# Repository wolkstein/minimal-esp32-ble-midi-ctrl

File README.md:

# Minimal ESP32 BLE Midi Control Interface

This project is a minimal ESP32 BLE MIDI controller. It allows you to control MIDI devices wirelessly using Bluetooth Low Energy (BLE) technology. The controller is designed to be compact and easy to use, making it ideal for musicians and performers.

## Features

- BLE MIDI connectivity
- Compact and portable design
- Easy-to-use interface
- Easy-to-use Web UI to make settings
- Online Firmware Update
- With Ardour and Harrison Mixbus compatible midi_map file
- as Platformio Project (esp32 arduino framework)

## Parts
- ESP32-S3-Mini
- 5 momentary button switches
- 5 10k resistors
- breadboard
- optional rgb led ws28xx

## PCB Version with Lipo and Battery Charger

PCB:

Housing:

## Getting Started

To get started with the project, follow these steps:

1. Clone the repository: `$ git clone https://github.com/wolkstein/minimal-esp32-ble-midi-ctrl`
2. Open as Platformio Project for example with VSC Pio Extension
3. Connect your ESP32 device to your computer via USB.
4. Change the platformio.ini as you need
5. Press PIO upload button
6. Your ESP32 BLE MIDI controller is now ready to use!

## Contributing

Contributions are welcome! If you have any ideas, suggestions, or bug reports, please open an issue or submit a pull request.

## License

This project is licensed under the GNU General Public License v3.0. See the [LICENSE](LICENSE) file for more information.

## Linux howto BlueZ with MIDI over BLE Support

Nice Howto from Peter P:

https://tttapa.github.io/Pages/Ubuntu/Software-Installation/BlueZ.html

After compiling BlueZ, Little Helper shown in Catja App

## Ardour / Mixbus Midi Setup

- For example copy the Midi Map file from this Repo like this:
```bash
cp DAW_MIDI_MAPS/ArdourAndHarrisonMixbus/midi_mapsLittle_Helper.map ~/.config/ardour6/midi_maps
```
- Now you can open the Edit-Preferences Window in Ardour, and under Control Surfaces, select Generic Midi
- Press Show Protocol Settings
- Now you can select "Little_Helper" in Midi Bindings dropdown
- if Little Helper is already connected via bluetooth you can make connection in Incoming Midi Dropdown like in the Image below
- Done  

---
## Some more pictures of how it is used

### All parts

### Guitar attachment

### Web interface

---
## Simple Manual

### First Wi-Fi Connection and Settings

#### To connect to the built-in access point, follow these steps:

1. Power on your ESP32 BLE MIDI controller while pressing Btn 4 and 5
2. Wait til LED becomes Blue
3. Once initialized, the controller will start broadcasting its own access point (AP) named "LittleHelperAP-xxx"
4. On your computer or mobile device, go to the Wi-Fi settings and connect to the "LittleHelperAP-xxx" network.
5. Open a web browser and enter the following URL: `http://192.168.8.1`.
6. You will be redirected to the controller's web interface.
7. In the web interface, navigate to the "Settings" Tab.

After completing the initial steps, the device is now capable of connecting to a local network. If the user desires, they can hold down buttons 4 and 5 while powering down the device. This will allow the device to connect to a local Wi-Fi network and start the web UI for making MIDI settings, if necessary.

## Firmware Update over WiFi Connection

To update the firmware of your ESP32 BLE MIDI controller over a WiFi connection, follow these steps:

1. Ensure that your ESP32 BLE MIDI controller is connected to your local WiFi network. You can do this by navigating to the "Settings" tab in the controller's web interface and entering your WiFi credentials.

2. Once connected, go to the Settings Tab and check the label that displays the current firmware version (e.g., s3miniVx).

3. Visit the GitHub project page for Little Helper and go to the "Binary" folder (https://github.com/wolkstein/minimal-esp32-ble-midi-ctrl/tree/main/bin) to check if there is a newer firmware available. Look for a firmware version number that is higher than the one displayed in the firmware label.

4. If a newer firmware is available, you can proceed with the update.

5. In the Settings Tab, click the "Try Update" button to request the firmware update.

6. After clicking the button, you will see a message saying "Update Requested, need Reboot".

7. Turn off the power to your ESP32 BLE MIDI controller by switching the power switch to the "off" position and removing the USB cable.

8. Power on the device again either by switching the power switch back on or by connecting the USB cable.

9. Wait for the LED on the device to turn yellow. This indicates that the device is in update mode and is connected to your local network.

10. If the LED starts blinking purple, it means that the update process is running. Wait until the LED switches back to its normal red or green light. If the LED does not blink purple, it means that the device has rebooted without performing the update.

11. If the update fails, you can simply try again. If something goes wrong during the update, the previous firmware will be automatically recovered.

12. If the update is successful, you can reconnect to the web interface and check the firmware version label to confirm the update.

---
# Button Combinations at Power up

This section describes the button combinations and their corresponding functions that can be used during power up.
Btn 1 to btn 5 from left to right.

| Button Combination | Function                                                  |
| ----------------- | --------------------------------------------------------- |
| o o o x x         | Connect To Local Wifi Network and enable Web UI            |
| o o x x x         | Start AP Mode and enable Web UI                            |
| x x o o o         | Reset Midi Settings to Default                            |
| x o x o o         | Reset Midi Settings and Wifi Settings to Default          |

x = pressed,
o = released

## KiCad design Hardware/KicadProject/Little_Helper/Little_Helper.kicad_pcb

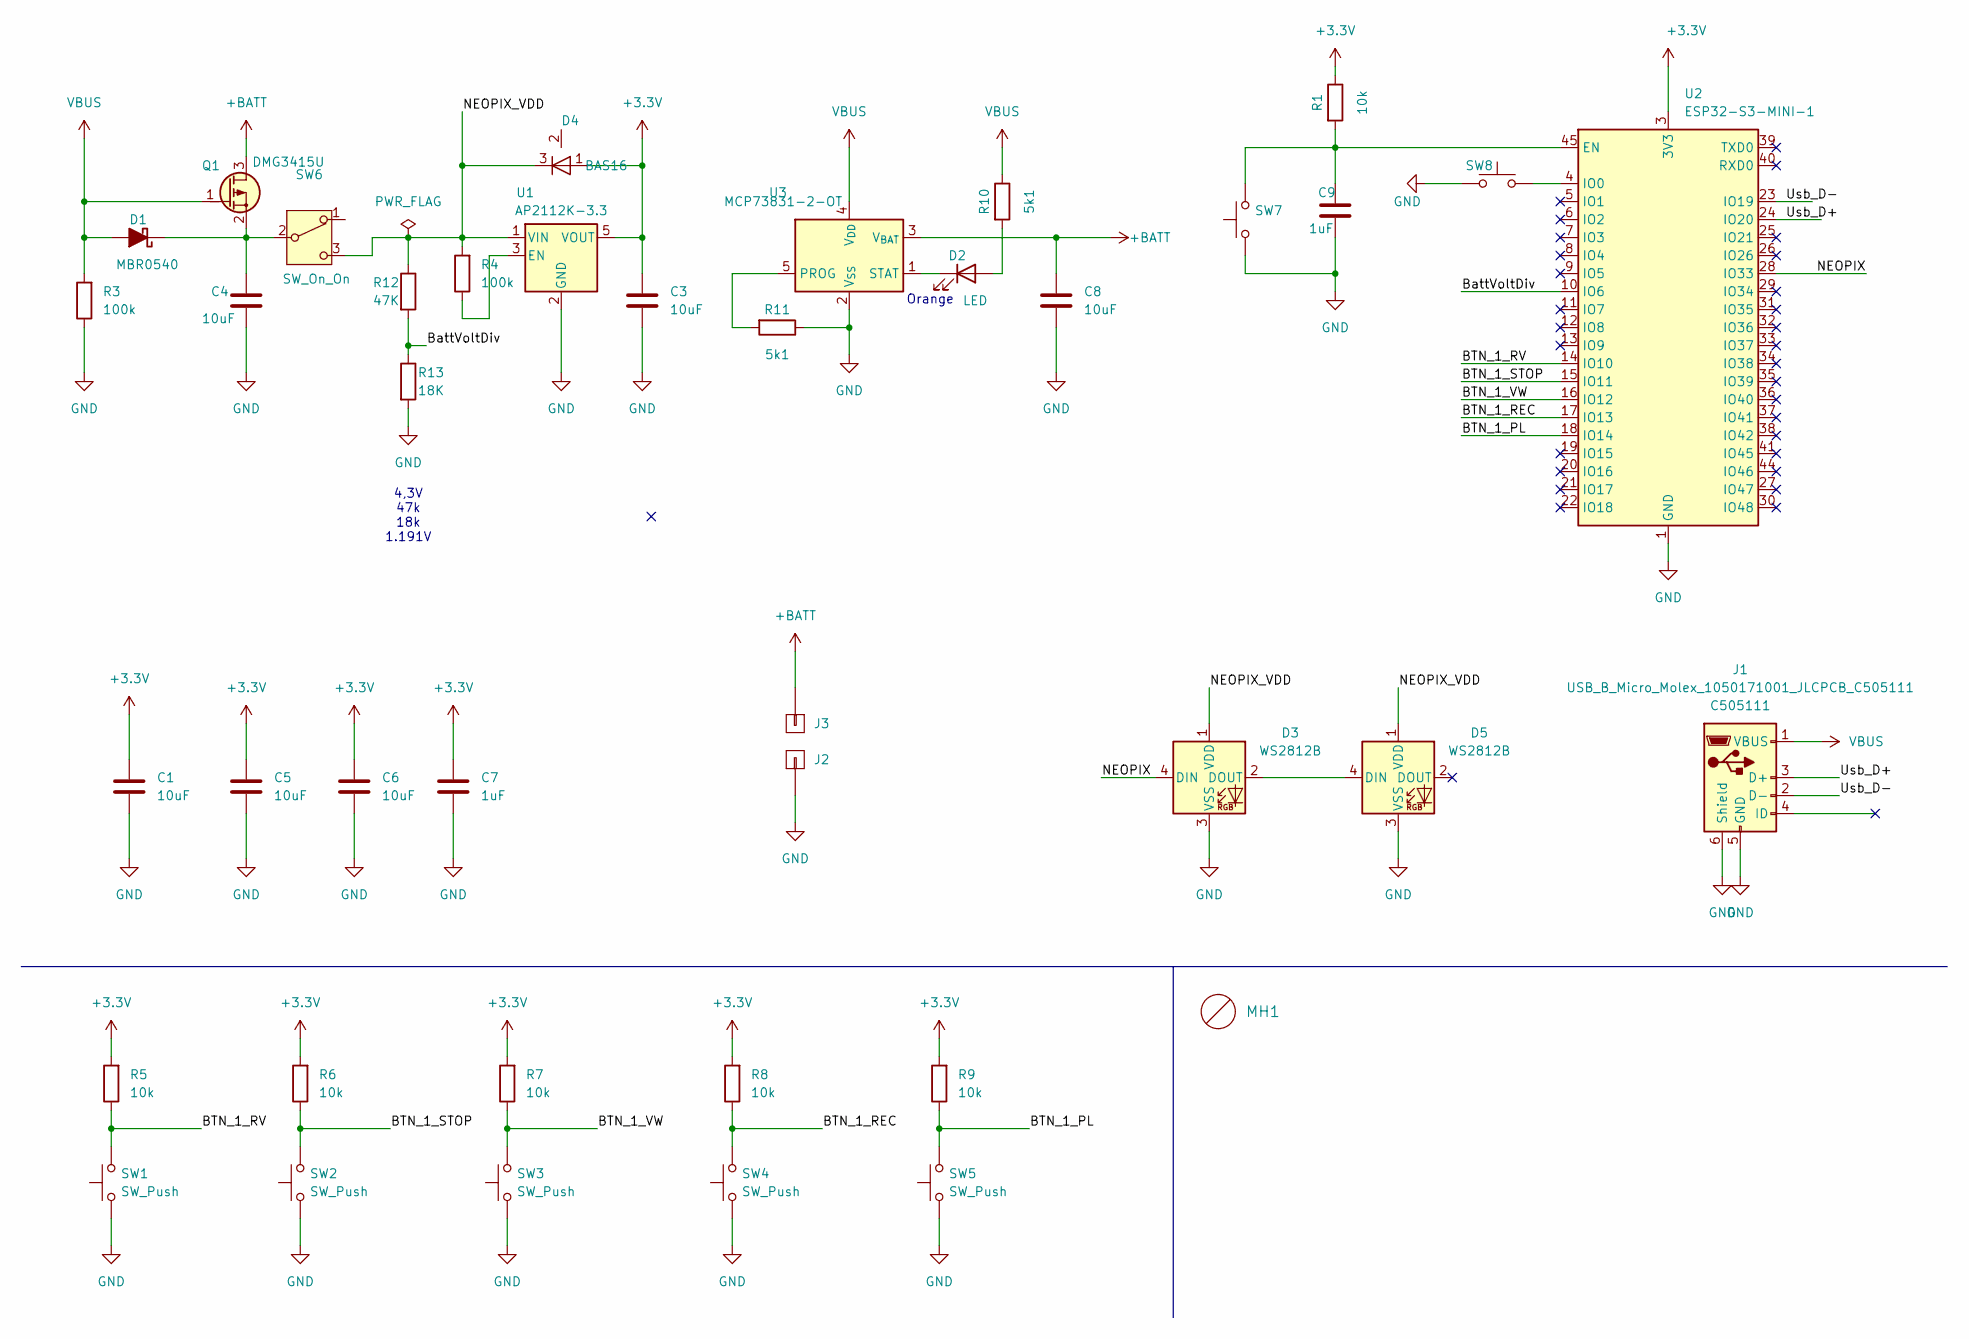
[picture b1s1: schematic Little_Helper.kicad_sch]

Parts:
C1, C3, C4, C5, C6, C8: 10uF; C_0805_2012Metric; LCSC C1713
C7, C9: 1uF; C_0603_1608Metric; LCSC C1592
D1: MBR0540; D_SOD-123; LCSC C78545
D2: LED; LED_0603_1608Metric; LCSC C2286
D3, D5: WS2812B; LED_WS2812B_JLCPCB_5.0x5.0mm_P3.2mm; LCSC C2843785
D4: BAS16; sot_23; MPN BAS16,215; LCSC C79997
J1: USB_B_Micro_Molex_1050171001_JLCPCB_C505111; USB_Micro-B_Molex-105017-0001; MPN 1050171001; LCSC Part # C505111
J2, J3: SOLDER_CON_5x2_TOP; solder_con_5x2_top
MH1: fit_3_1
Q1: DMG3415U; SOT-23; LCSC C96616
R1, R5, R6, R7, R8, R9: 10k; R_0805_2012Metric; LCSC C17414
R3, R4: 100k; R_0805_2012Metric; LCSC C149504
R10, R11: 5k1; R_0805_2012Metric; LCSC C115316
R12: 47K; r2012; LCSC Part # C17713
R13: 18K; r2012; LCSC Part # C17506
SW1, SW2, SW3, SW4, SW5: SW_Push; SW_PUSH_6mm_H5mm
SW6: SW_On_On; SW_SPDT_PCM12; MPN MK-12C02-G020; LCSC Part # C963206
SW7, SW8: SW_Tactile_Small; SW_SPST_TS-1088-AR02016; MPN TS-1088-AR02016; LCSC Part # C720477
U1: AP2112K-3.3; SOT-23-5; LCSC C51118
U2: ESP32-S3-MINI-1; ESP32-S2-MINI-1; LCSC C2913206
U3: MCP73831-2-OT; SOT-23-5; LCSC C424093

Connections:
+3.3V: C1.1, C3.1, C5.1, C6.1, C7.1, D4.1 (A), R1.1, R5.2, R6.2, R7.2, R8.2, R9.2, U1.5 (VOUT), U2.3 (3V3)
+BATT: C8.1, J3.1, Q1.3 (D), U3.3 (V_{BAT})
/BTN_1_PL: R9.1, SW5.2, U2.18 (IO14)
/BTN_1_REC: R8.1, SW4.2, U2.17 (IO13)
/BTN_1_RV: R5.1, SW1.2, U2.14 (IO10)
/BTN_1_STOP: R6.1, SW2.2, U2.15 (IO11)
/BTN_1_VW: R7.1, SW3.2, U2.16 (IO12)
/BattVoltDiv: R12.2, R13.1, U2.10 (IO6)
/NEOPIX: D3.4 (DIN), U2.28 (IO33)
/NEOPIX_VDD: D3.1 (VDD), D4.3 (K), D5.1 (VDD), R4.2, R12.1, SW6.3 (C), U1.1 (VIN)
/Usb_D+: J1.3 (D+), U2.24 (IO20)
/Usb_D-: J1.2 (D-), U2.23 (IO19)
GND: C1.2, C3.2, C4.2, C5.2, C6.2, C7.2, C8.2, C9.2, D3.3 (VSS), D5.3 (VSS), J1.5 (GND), J1.6 (Shield), J2.1, R3.1, R11.1, R13.2, SW1.1, SW2.1, SW3.1, SW4.1, SW5.1, SW7.1 (A), SW8.1 (A), U1.2 (GND), U2.1 (GND), U2.2 (GND), U2.42 (GND), U2.43 (GND), U2.46 (GND), U2.47 (GND), U2.48 (GND), U2.49 (GND), U2.50 (GND), U2.51 (GND), U2.52 (GND), U2.53 (GND), U2.54 (GND), U2.55 (GND), U2.56 (GND), U2.57 (GND), U2.58 (GND), U2.59 (GND), U2.60 (GND), U2.61 (GND), U2.62 (GND), U2.63 (GND), U2.64 (GND), U2.65 (GND), U3.2 (V_{SS})
unnamed: C4.1, D1.1 (K), Q1.2 (S), SW6.2 (B)
unnamed: D2.2 (A), R10.2
unnamed: D2.1 (K), U3.1 (STAT)
unnamed: D3.2 (DOUT), D5.4 (DIN)
unnamed: R4.1, U1.3 (EN)
unnamed: C9.1, R1.2, SW7.2 (A), U2.45 (EN)
unnamed: SW8.2 (A), U2.4 (IO0)
unnamed: R11.2, U3.5 (PROG)
VBUS: D1.2 (A), J1.1 (VBUS), Q1.1 (G), R3.2, R10.1, U3.4 (V_{DD})

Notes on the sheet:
4,3V 47k 18k 1.191V
Orange

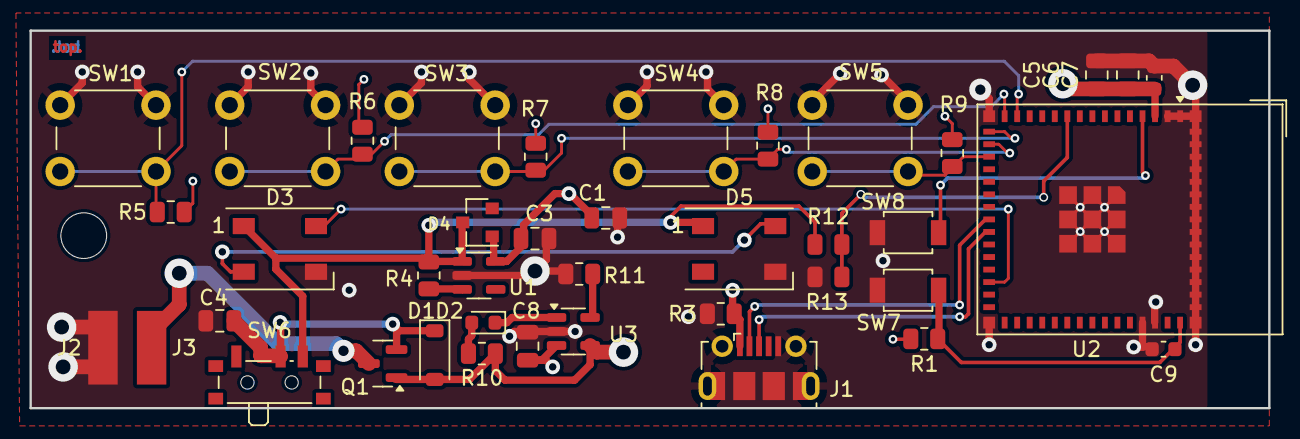
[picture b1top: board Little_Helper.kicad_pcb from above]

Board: 4 copper layers, 84.0 x 25.6 mm, 41 parts (0 on the bottom side), 22 nets.

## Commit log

2024-05-16 Add Pio Project folder and Project files
2024-05-16 Add Harware Design Files(Template). Kicad Project and Freecad Project. Add MidiMaps for Ardour and HarrisonMixbus DAW.
2024-05-16 Add License Info
2024-05-16 fix log_i debug info text
2024-05-17 better longpress handling add readme.md add WS28xx rgb LED (optional)
2024-05-17 add WX2812B state Info Led
2024-05-17 copy README.md to Project root dir
2024-05-20 After the decision was made for the ESP32-S3-Mini, the first size experiments for the case
2024-05-20 fix some library mismatch
2024-05-25 add tactile buttons
2024-06-08 board in progress
2024-06-14 some changes on pads
2024-06-14 change usb micro connector
2024-06-14 10uf cap from 0603 to 0805
2024-06-14 save prev changes
2024-06-14 add lsc parts
2024-06-15 select the right footprint
2024-06-15 Change Putton Switch
2024-06-15 Change Boot and Reset BTN
2024-06-20 pcb layout v1.0 done
2024-06-21 First simple version of a case
2024-06-21 Add Pcb Step file (CAD)
2024-06-21 Add PCB WRL file
2024-06-21 switch to board V1.1 version
2024-06-21 work on howto and housing
2024-06-21 Add Image Catja and Little Helper
2024-06-21 add missing image
2024-06-21 add freecad image to readme
2024-06-21 new Cover
2024-06-21 edit Readme
2024-06-21 add som PCB images
2024-06-21 export 1.1 wrl
2024-06-21 v1.1 wrl png
2024-06-23 edit pcb and footprints for pcb rev1.1
2024-06-23 restor cover
2024-06-23 pcb v1.1 add second ws2812 led
2024-06-23 update 3d files
2024-06-24 freecad change pcb step file against wrl file
2024-07-04 create little-helperesp32-s3-mini env and board file
2024-07-04 new firmware woith midi maps and AceButton Button class
2024-07-05 v1.0 on esp32-s3-mini and esp32-wroom
2024-07-05 esp32 wroom module bug
2024-07-06 add preferences and platine image
2024-07-06 remove esp32dev target. default target is esp32-s3-mini add webui, and start to migrate configoptions for btn 1 - 5 in webui
2024-07-06 fix typo
2024-07-06 change led color function
2024-07-07 add more preferences options
2024-07-08 add missing main.h file and webui btn2 finished
2024-07-08 add spi psram build flag
2024-07-09 generate Buttons for Ui more dynamicly
2024-07-10 finish first simple config ui
2024-07-10 fix pref. blename issue
2024-07-11 UI Add Selector for Button Transition and Button behave. And the control logic
2024-07-12 add Colorhooser Button
2024-07-13 Add Guitar attachment with suction cup
2024-07-13 add some Guitar attachment images
2024-07-13 work on documentation
2024-07-13 fix wrong filenames
2024-07-13 fix filename
2024-07-13 add webinterface images
2024-07-13 add info image on to
2024-07-16 add batterie voltage divider. add colorchooser. this commit produce an major bug in button mapping. 2. Map is completly broken.
2024-07-17 fix broken mapping bug
2024-07-25 smal modification on cad file
2024-07-26 add more maps
2024-07-26 add pc callback to change active map via midi
2024-07-28 use global vars use without function argument
2024-07-29 mmc implementation under linux. no option to test mmc here.
2024-07-29 finish mmc integration.
2024-07-30 Stable WEBUI
2024-07-30 add firmware file for ota update
2024-07-30 start simple ota implementation
2024-07-30 Testversion OTA Update from Github
2024-07-30 change fw v2
2024-07-31 create smaller testfirmware
2024-07-31 testing on fw update. this need some testfiles.
2024-07-31 add test firmware
2024-07-31 more testversions
2024-07-31 finish first simple version with online firmware update from github
2024-07-31 change firmware nr to 2
2024-07-31 Add the final Firmware - first online update is out
2024-07-31 create new firmware bin file
2024-07-31 add new firmware bin and disable serial output whole flashing
2024-08-01 new firmware bin released
2024-08-01 edit readme an add a simple manual to connect to local network
2024-08-01 fix spelling
2024-08-02 small change in housing cad. make platform fix that compiling on other linux pc's ends in a running system
2024-08-03 compile on ubuntu 24.04 LTS
2024-10-01 Faster BLE Conect after Power
2024-10-01 release new firmware s3miniV6.bin. faster ble conection after powering device
2025-02-06 add firmware v7 bin file
2025-02-06 add cc toggle function. release firmare V8
2025-02-23 simple cortex control test
2025-02-23 new branch for simple midi control
2025-02-23 Me no dev webserver on github
2025-02-23 change ESPAsyncWebServer url to github
2025-02-26 finish simplest midi ctl with feedback for 2 maps. map1 Cortex Foot Switch A B C, map2 Foot switch E F H.
